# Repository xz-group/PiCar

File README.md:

PiCar Project
========================

Purpose
--------

The PiCar project is a miniature four-wheeled car powered by a Raspberry Pi 3 board. 
This lab-scale autonomous research platform is easy to build and modify. A camera and LIDAR mounted on the car allows for complex computer vision algorithms. 

This repository contains all the software and hardware source files required to duplicate the car, including:
* Chassis 3D printing, and CAD sources.
* Raspberry Pi 3 breakout PCB to connect peripherals and draw power from LiPo battery.
* Source code of the following sofware modules capable of:
 * Acquire wheel RPM data using encoder.
 * Acquire acceleration, angular velocity, and compass data from an I²C LSM9DS1 IMU.
 * Acquire video data from a Raspberry Pi NoIR camera.
 * Perform real-time computer vision using camera data.
 * Control the speed of brushed DC motor.

Documentation 
--------------
- http://picar.readthedocs.io (migration in progress)
- https://github.com/xz-group/PiCar/wiki (old)

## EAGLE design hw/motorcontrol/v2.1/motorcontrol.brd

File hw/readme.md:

The current version of the PiCar does not use a separate motor control board. 
Check documentation for hardware info.

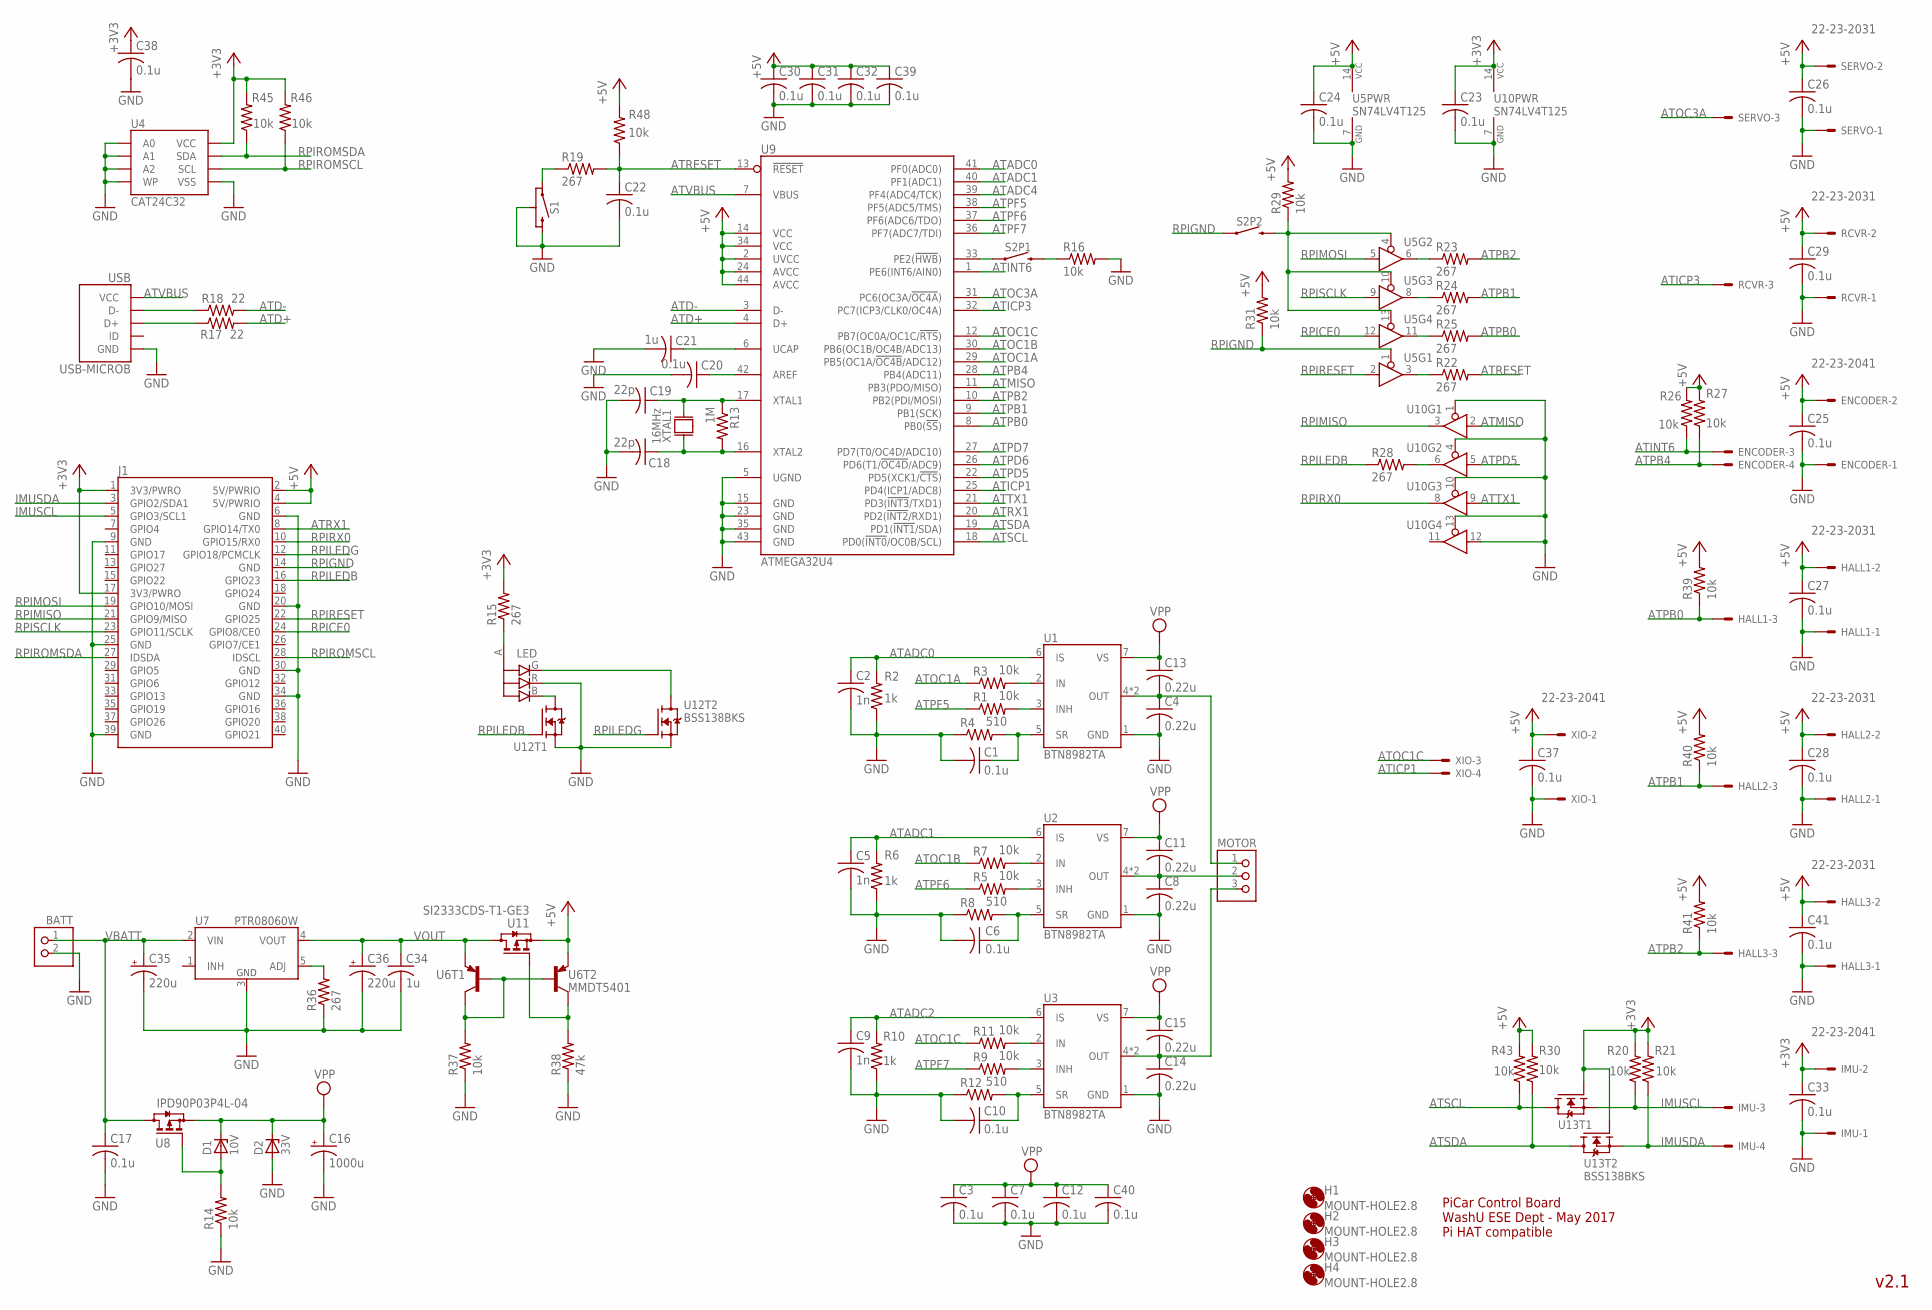
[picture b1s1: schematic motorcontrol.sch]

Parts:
BATT: ULTRAFIT_2CIRCVCLIP; ULTRAFIT_2CIRC_VERTCLIP
C1, C3, C6, C7, C10, C12, C17, C20, C22, C23, C24, C25, C26, C27, C28, C29, C30, C31, C32, C33, C37, C38, C39, C40, C41: 0.1u; C1206
C2, C5, C9: 1n; C1206
C4, C8, C11, C13, C14, C15: 0.22u; C1206
C16: 1000u; E5-10,5
C18, C19: 22p; C1206
C21, C34: 1u; C1206
C35, C36: 220u; E3,5-8
D1: 10V; SOD123
D2: 33V; SMA
ENCODER: 22-23-2041
H1, H2, H3, H4: MOUNT-HOLE2.8; 2,8
HALL1, HALL2, HALL3: 22-23-2031
IMU: 22-23-2041
J1: RPIHEADER_2.54-SMD; RPI_SMD
LED: LED_3COLOR_COMMONA1411; 150141M173100
MOTOR: ULTRAFIT_3CIRCVCLIP; ULTRAFIT_3CIRC_VERTCLIP
R1, R3, R5, R7, R9, R11, R14, R16, R20, R21, R26, R27, R29, R30, R31, R37, R39, R40, R41, R43, R45, R46, R48: 10k; R1206
R2, R6, R10: 1k; R1206
R4, R8, R12: 510; R1206
R13: 1M; R1206
R15, R19, R22, R23, R24, R25, R28, R36: 267; R1206
R17, R18: 22; R1206
R38: 47k; R1206
RCVR: 22-23-2031
S1: SWITCH-GND; B3F-312X
S2: A6HF-2DIP
SERVO: 22-23-2031
U1, U2, U3: BTN8982TA; TO263-7
U4: CAT24C32; SOIC8
U5, U10: SN74LV4T125; TSSOP14
U6: MMDT5401; SOT363
U7: PTR08060W; EDP_MODULE
U8: IPD90P03P4L-04; TO252-3-11
U9: ATMEGA32U4; TQFP44
U11: SI2333CDS-T1-GE3; SOT23-3
U12, U13: BSS138BKS; SOT363
USB: USB-MICROB; FCI-10103594-0001LF
XIO: 22-23-2041
XTAL1: 16MHz; ABLS7M2

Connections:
+3V3: C23.1, C33.1, C38.1, IMU.2, J1.1 (3V3/PWRO), J1.17 (3V3/PWRO), R15.2, R20.2, R21.2, R45.2, R46.2, U4.8 (VCC), U10.14 (VCC), U13.2 (G), U13.5 (G)
+5V: C24.1, C25.1, C26.1, C27.1, C28.1, C29.1, C30.1, C31.1, C32.1, C37.1, C39.1, C41.1, ENCODER.2, HALL1.2, HALL2.2, HALL3.2, J1.2 (5V/PWRIO), J1.4 (5V/PWRIO), R26.2, R27.2, R29.2, R30.2, R31.2, R39.2, R40.2, R41.2, R43.2, R48.2, RCVR.2, SERVO.2, U5.14 (VCC), U6.4 (E), U9.2 (UVCC), U9.14 (VCC), U9.24 (AVCC), U9.34 (VCC), U9.44 (AVCC), U11.2 (S), XIO.2
ATADC0: C2.1, R2.2, U1.6 (IS), U9.41 (PF0(ADC0))
ATADC1: C5.1, R6.2, U2.6 (IS), U9.40 (PF1(ADC1))
ATD+: R17.2, U9.4 (D+)
ATD-: R18.2, U9.3 (D-)
ATICP1: U9.25 (PD4(ICP1/ADC8)), XIO.4
ATICP3: RCVR.3, U9.32 (PC7(ICP3/CLK0/OC4A))
ATINT6: ENCODER.3, R26.1, U9.1 (PE6(INT6/AIN0))
ATMISO: U9.11 (PB3(PDO/MISO)), U10.2 (I)
ATOC1A: R3.1, U9.29 (PB5(OC1A/!OC4B!/ADC12))
ATOC1B: R7.1, U9.30 (PB6(OC1B/OC4B/ADC13))
ATOC1C: R11.1, U9.12 (PB7(OC0A/OC1C/!RTS!)), XIO.3
ATOC3A: SERVO.3, U9.31 (PC6(OC3A/!OC4A!))
ATPB0: HALL1.3, R25.2, R39.1, U9.8 (PB0(!SS!))
ATPB1: HALL2.3, R24.2, R40.1, U9.9 (PB1(SCK))
ATPB2: HALL3.3, R23.2, R41.1, U9.10 (PB2(PDI/MOSI))
ATPB4: ENCODER.4, R27.1, U9.28 (PB4(ADC11))
ATPD5: U9.22 (PD5(XCK1/!CTS!)), U10.5 (I)
ATPF5: R1.1, U9.38 (PF5(ADC5/TMS))
ATPF6: R5.1, U9.37 (PF6(ADC6/TDO))
ATPF7: R9.1, U9.36 (PF7(ADC7/TDI))
ATRESET: C22.1, R19.2, R22.2, R48.1, U9.13 (!RESET!)
ATRX1: J1.8 (GPIO14/TX0), U9.20 (PD2(!INT2!/RXD1))
ATSCL: R43.1, U9.18 (PD0(!INT0!/OC0B/SCL)), U13.6 (D)
ATSDA: R30.1, U9.19 (PD1(!INT1!/SDA)), U13.3 (D)
ATTX1: U9.21 (PD3(!INT3!/TXD1)), U10.9 (I)
ATVBUS: U9.7 (VBUS), USB.1 (VCC)
GND: BATT.2, C1.2, C2.2, C3.2, C4.2, C5.2, C6.2, C7.2, C8.2, C9.2, C10.2, C12.2, C14.2, C16.-, C17.2, C18.2, C19.2, C20.2, C21.2, C22.2, C23.2, C24.2, C25.2, C26.2, C27.2, C28.2, C29.2, C30.2, C31.2, C32.2, C33.2, C34.2, C35.-, C36.-, C37.2, C38.2, C39.2, C40.2, C41.2, D2.A, ENCODER.1, HALL1.1, HALL2.1, HALL3.1, IMU.1, J1.6 (GND), J1.9 (GND), J1.20 (GND), J1.25 (GND), J1.30 (GND), J1.34 (GND), J1.39 (GND), LED.R, R2.1, R4.1, R6.1, R8.1, R10.1, R12.1, R14.1, R16.2, R36.1, R37.1, R38.1, RCVR.1, S1.2, S1.3 (GND), S1.4 (GND), SERVO.1, U1.1 (GND), U2.1 (GND), U3.1 (GND), U4.1 (A0), U4.2 (A1), U4.3 (A2), U4.4 (VSS), U4.7 (WP), U5.7 (GND), U7.3 (GND), U9.5 (UGND), U9.15 (GND), U9.23 (GND), U9.35 (GND), U9.43 (GND), U10.1 (OE), U10.4 (OE), U10.7 (GND), U10.10 (OE), U10.12 (I), U10.13 (OE), U12.1 (S), U12.4 (S), USB.5 (GND), USB.GND1 (GND), USB.GND2 (GND), USB.GND3 (GND), USB.GND4 (GND), XIO.1
IMUSCL: IMU.3, J1.5 (GPIO3/SCL1), R20.1, U13.1 (S)
IMUSDA: IMU.4, J1.3 (GPIO2/SDA1), R21.1, U13.4 (S)
unnamed: R1.2, U1.3 (INH)
unnamed: R38.2, U6.3 (C), U11.1 (G)
unnamed: C19.1, R13.1, U9.17 (XTAL1), XTAL1.2
unnamed: R3.2, U1.2 (IN)
unnamed: C6.1, R8.2, U2.5 (SR)
unnamed: R5.2, U2.3 (INH)
unnamed: C18.1, R13.2, U9.16 (XTAL2), XTAL1.1
unnamed: S2.P1.1 (1), U9.33 (PE2(!HWB!))
unnamed: R7.2, U2.2 (IN)
unnamed: LED.A, R15.1
unnamed: R28.2, U10.6 (O)
unnamed: R16.1, S2.P1.2 (2)
unnamed: R37.2, U6.2 (B), U6.5 (B), U6.6 (C)
unnamed: LED.B, U12.6 (D)
unnamed: R9.2, U3.3 (INH)
unnamed: R18.1, USB.2 (D-)
unnamed: R11.2, U3.2 (IN)
unnamed: R22.1, U5.3 (O)
unnamed: C20.1, U9.42 (AREF)
unnamed: C21.1, U9.6 (UCAP)
unnamed: D1.A, R14.2, U8.1 (G)
unnamed: LED.G, U12.3 (D)
unnamed: R19.1, S1.1
unnamed: C1.1, R4.2, U1.5 (SR)
unnamed: R17.1, USB.3 (D+)
unnamed: C10.1, R12.2, U3.5 (SR)
unnamed: R23.1, U5.6 (O)
unnamed: R24.1, U5.8 (O)
unnamed: R25.1, U5.11 (O)
unnamed: R36.2, U7.5 (ADJ)
OUT1: C4.1, C13.2, MOTOR.1, U1.4 (OUT), U1.8 (OUT)
OUT2: C8.1, C11.2, MOTOR.2, U2.4 (OUT), U2.8 (OUT)
OUT3: C14.1, C15.2, MOTOR.3, U3.4 (OUT), U3.8 (OUT)
RPICE0: J1.24 (GPIO8/CE0), U5.12 (I)
RPIGND: J1.14 (GND), R31.1, S2.P2.1 (1), U5.1 (OE)
RPILEDB: J1.16 (GPIO23), R28.1, U12.2 (G)
RPILEDG: J1.12 (GPIO18/PCMCLK), U12.5 (G)
RPIMISO: J1.21 (GPIO9/MISO), U10.3 (O)
RPIMOSI: J1.19 (GPIO10/MOSI), U5.5 (I)
RPIRESET: J1.22 (GPIO25), U5.2 (I)
RPIROMSCL: J1.28 (IDSCL), R46.1, U4.6 (SCL)
RPIROMSDA: J1.27 (IDSDA), R45.1, U4.5 (SDA)
RPIRX0: J1.10 (GPIO15/RX0), U10.8 (O)
RPISCLK: J1.23 (GPIO11/SCLK), U5.9 (I)
U5OE: R29.1, S2.P2.2 (2), U5.4 (OE), U5.10 (OE), U5.13 (OE)
VBATT: BATT.1, C17.1, C35.+, U7.2 (VIN), U8.2 (D)
VOUT: C34.1, C36.+, U6.1 (E), U7.4 (VOUT), U11.3 (D)
VPP: C3.1, C7.1, C11.1, C12.1, C13.1, C15.1, C16.+, C40.1, D1.C, D2.C, U1.7 (VS), U2.7 (VS), U3.7 (VS), U8.3 (S)

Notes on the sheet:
PiCar Control Board WashU ESE Dept - May 2017 Pi HAT compatible
v2.1

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
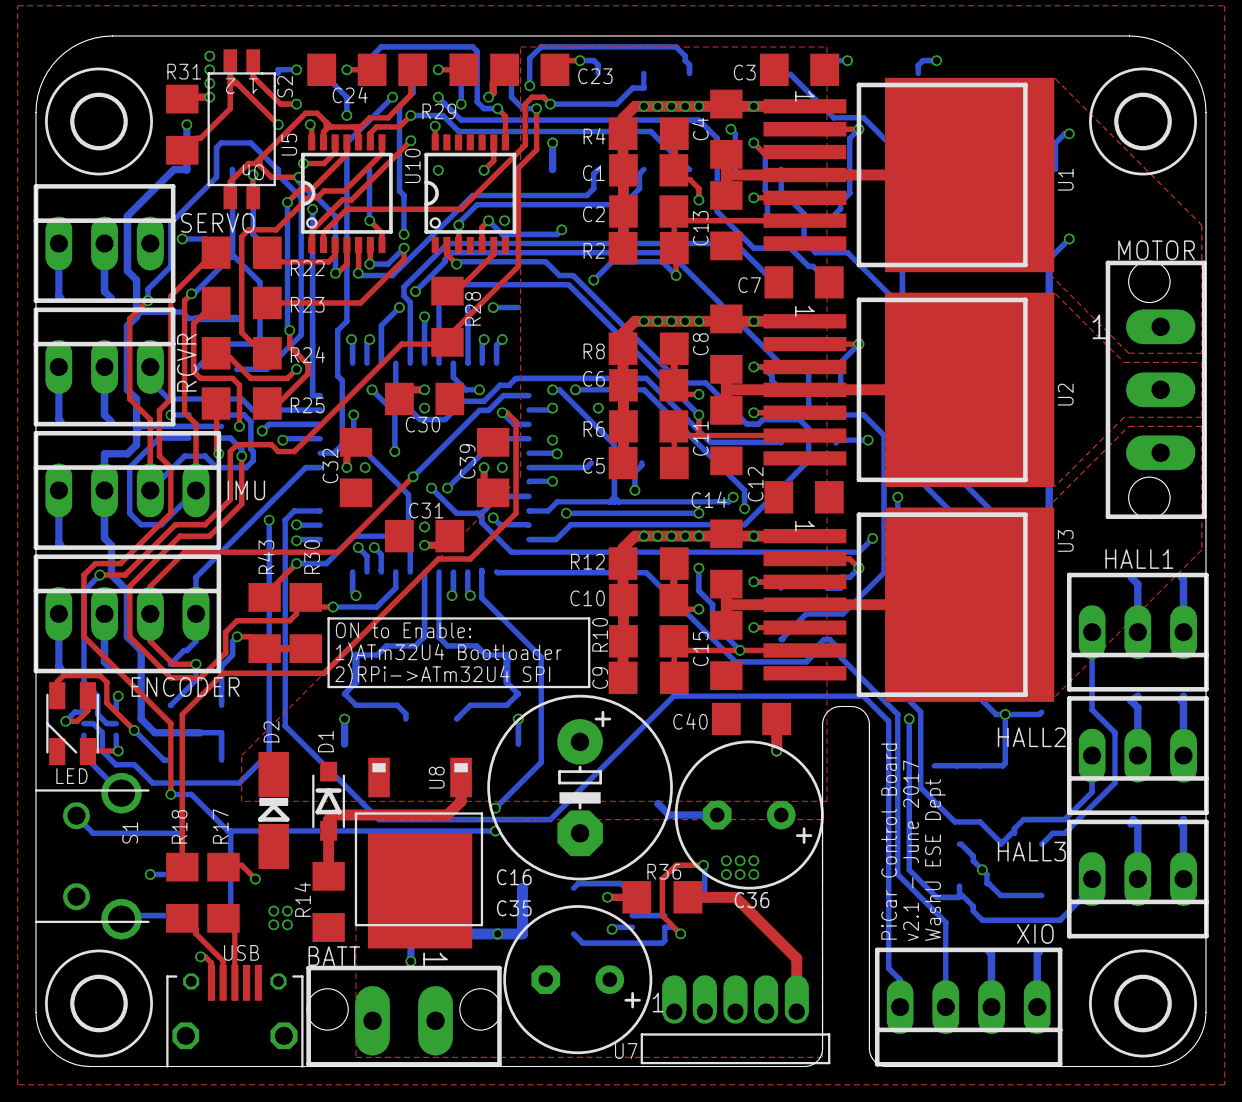
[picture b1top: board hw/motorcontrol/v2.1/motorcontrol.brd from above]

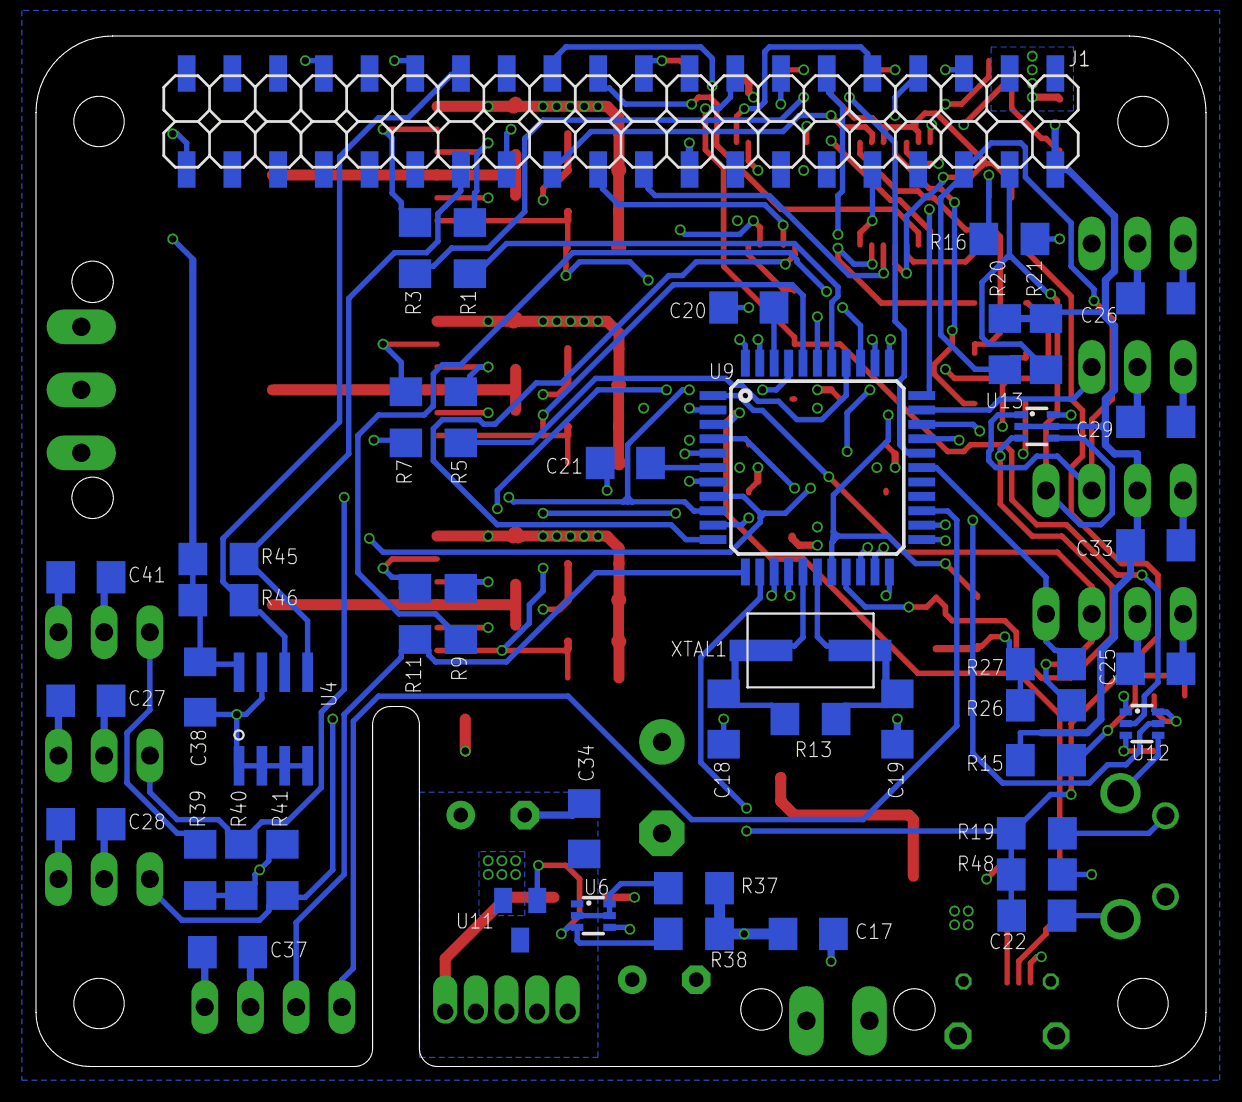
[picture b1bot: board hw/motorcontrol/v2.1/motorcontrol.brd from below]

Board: 4 copper layers, 65.0 x 57.2 mm, 117 parts (45 on the bottom side), 80 nets.

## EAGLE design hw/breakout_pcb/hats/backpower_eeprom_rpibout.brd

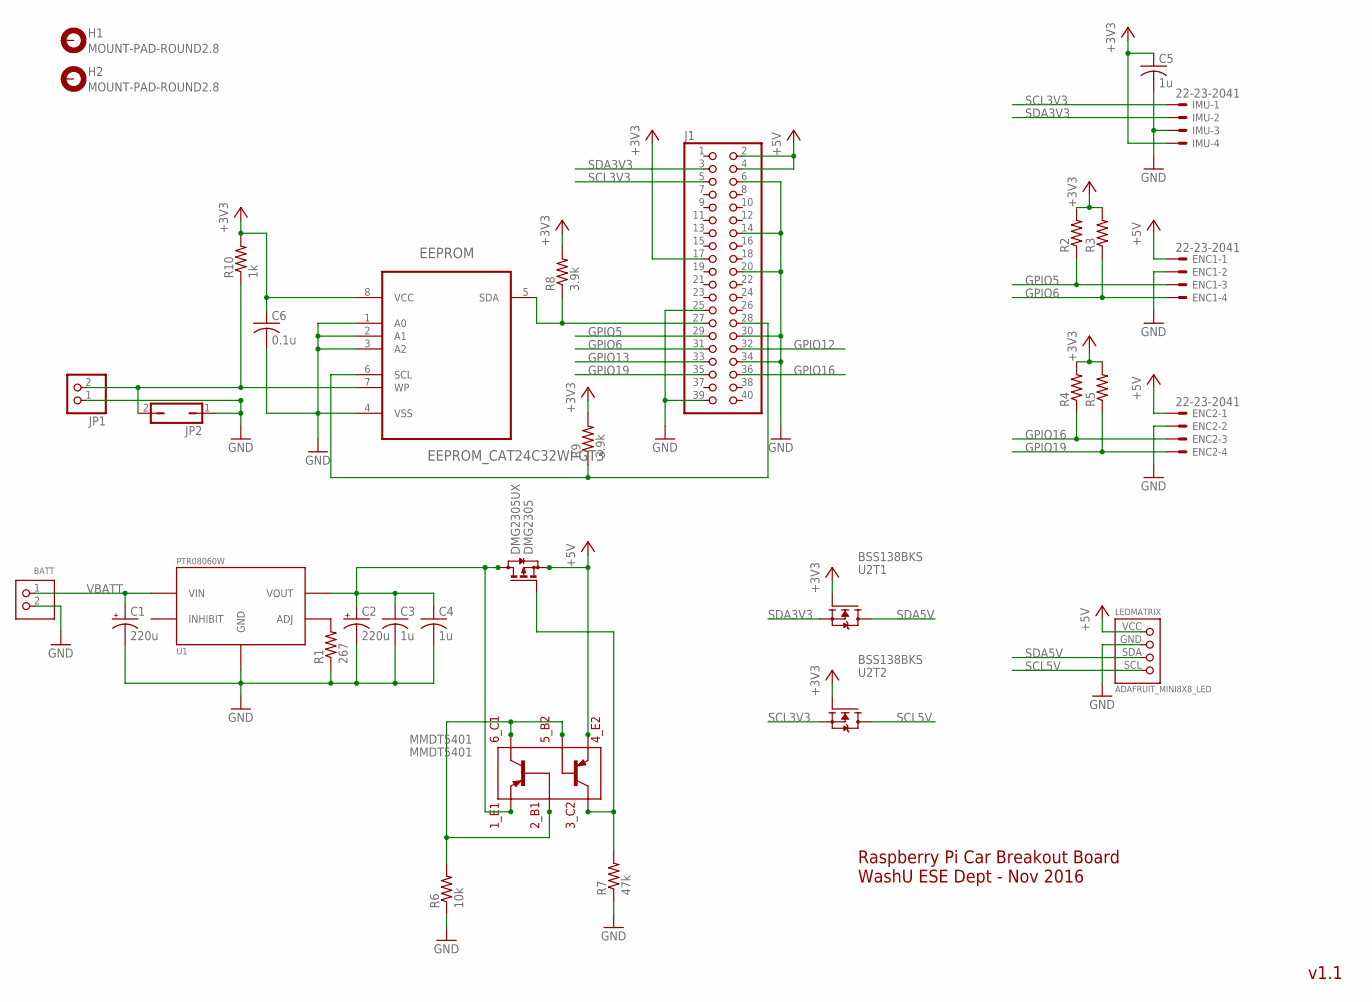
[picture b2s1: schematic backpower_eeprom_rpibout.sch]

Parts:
BATT: ULTRAFIT_2CIRC; ULTRAFIT_2CIRC_RANGLE
C1, C2: 220u; E3,5-8
C3, C4, C5: 1u; C1206
C6: 0.1u; C1206
DMG2305: DMG2305UX; SOT23-3
EEPROM: EEPROM_CAT24C32WI-GT3; SOIC-8
ENC1, ENC2: 22-23-2041
H1, H2: MOUNT-PAD-ROUND2.8; 2,8-PAD
IMU: 22-23-2041
J1: PINHD-2X20; 2X20
JP1: PINHD-1X2; 1X02
JP2: JP1Q; JP1
LEDMATRIX: ADAFRUIT_MINI8X8_LED; ADAFRUIT_MINI8X8_BACKPACK
MMDT5401: MMDT5401; SOT363
R1: 267; R1206
R2, R3, R4, R5: R-US_R1206; R1206
R6: 10k; R1206
R7: 47k; R1206
R8, R9: 3.9k; R1206
R10: 1k; R1206
U1: PTR08060W; EDP_MODULE
U2: BSS138BKS; SOT363

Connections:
+3V3: C5.1, C6.1, EEPROM.8 (VCC), IMU.4, J1.17, R2.2, R3.2, R4.2, R5.2, R8.2, R9.2, R10.2, U2.2 (G), U2.5 (G)
+5V: DMG2305.2 (S), ENC1.1, ENC2.1, J1.2, J1.4, LEDMATRIX.VCC, MMDT5401.1 (E1)
GND: BATT.2, C1.-, C2.-, C3.2, C4.2, C5.2, C6.2, EEPROM.1 (A0), EEPROM.2 (A1), EEPROM.3 (A2), EEPROM.4 (VSS), ENC1.2, ENC2.2, IMU.3, J1.6, J1.14, J1.20, J1.25, J1.30, J1.34, J1.39, JP1.1, JP2.1, LEDMATRIX.GND, R1.1, R6.1, R7.1, U1.P3 (GND)
GPIO5: ENC1.3, J1.29, R2.1
GPIO6: ENC1.4, J1.31, R3.1
GPIO12: J1.32
GPIO13: J1.33
GPIO16: ENC2.3, J1.36, R4.1
GPIO19: ENC2.4, J1.35, R5.1
unnamed: MMDT5401.2 (B1), MMDT5401.3 (C2), MMDT5401.5 (B2), R6.2
unnamed: R1.2, U1.P5 (ADJ)
unnamed: DMG2305.1 (G), MMDT5401.6 (C1), R7.2
unnamed: EEPROM.5 (SDA), J1.27, R8.1
unnamed: EEPROM.6 (SCL), J1.28, R9.1
unnamed: EEPROM.7 (WP), JP1.2, JP2.2, R10.1
SCL3V3: IMU.1, J1.5, U2.4 (S)
SCL5V: LEDMATRIX.SCL, U2.3 (D)
SDA3V3: IMU.2, J1.3, U2.1 (S)
SDA5V: LEDMATRIX.SDA, U2.6 (D)
VBATT: BATT.1, C1.+, U1.P2 (VIN)
VOUT: C2.+, C3.1, C4.1, DMG2305.3 (D), MMDT5401.4 (E2), U1.P4 (VOUT)

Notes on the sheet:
v1.1
Raspberry Pi Car Breakout Board WashU ESE Dept - Nov 2016

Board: 2 copper layers, 31 parts (0 on the bottom side), 19 nets, no tracks yet.

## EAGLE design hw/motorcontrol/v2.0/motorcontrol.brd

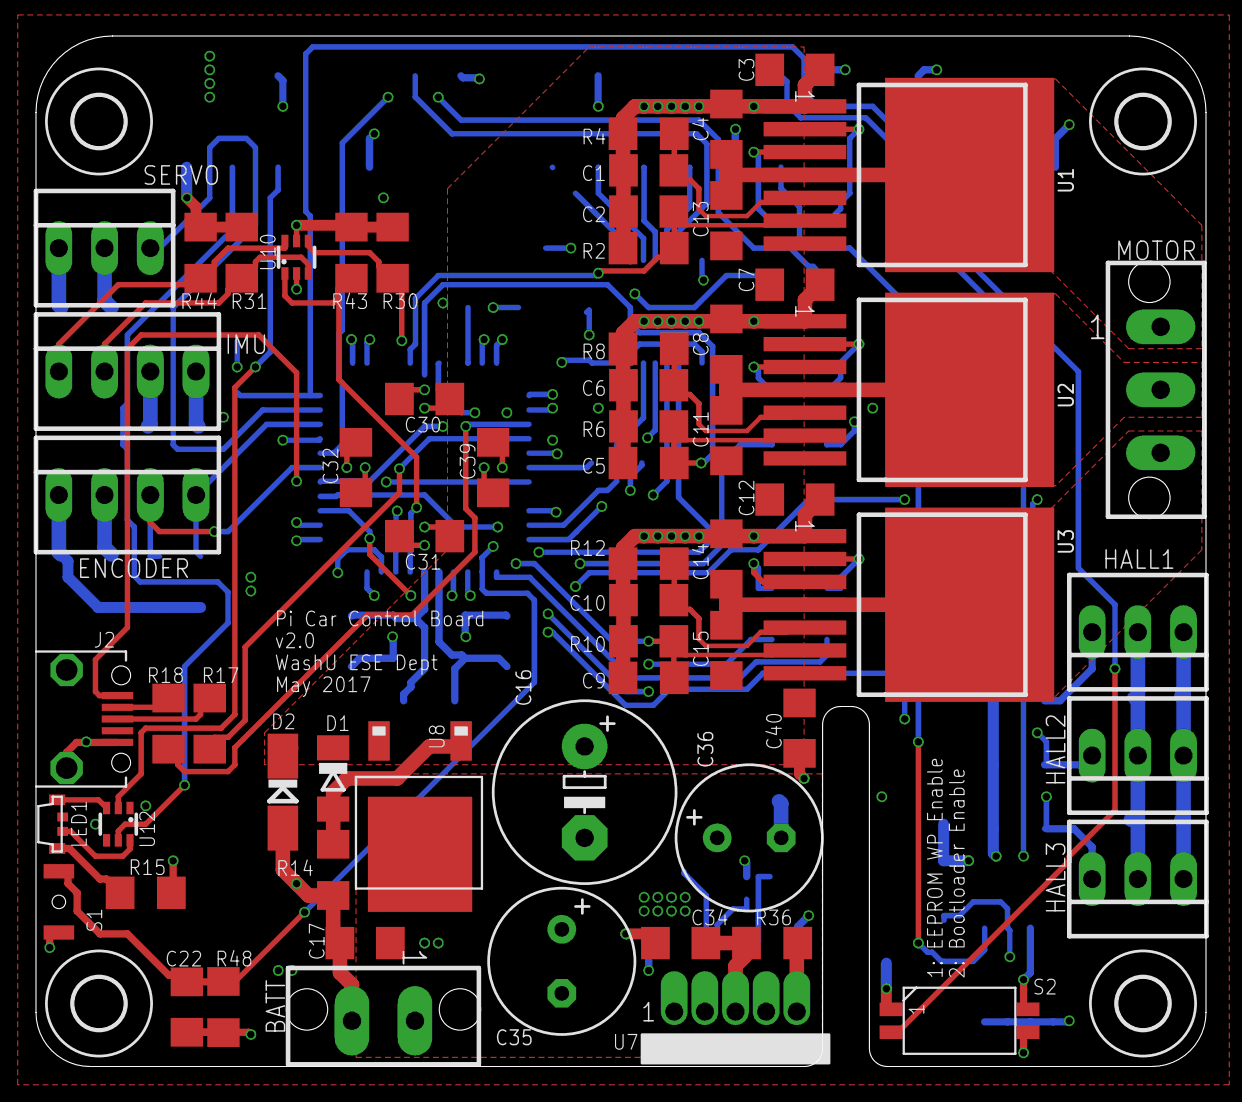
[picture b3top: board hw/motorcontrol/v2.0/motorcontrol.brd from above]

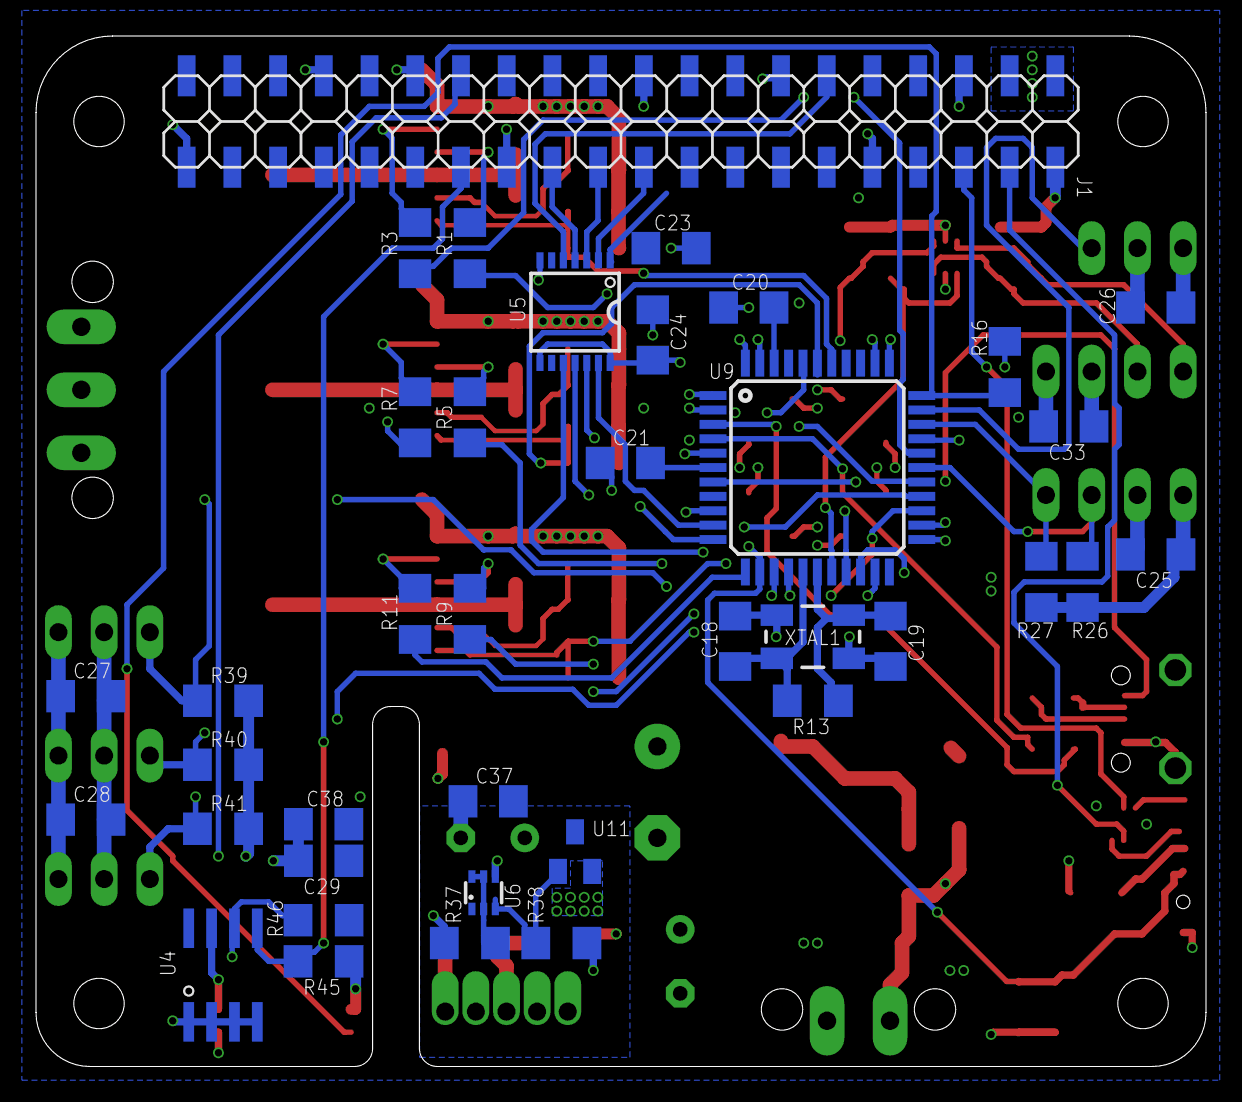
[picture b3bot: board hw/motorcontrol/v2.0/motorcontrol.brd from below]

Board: 4 copper layers, 65.0 x 57.2 mm, 105 parts (37 on the bottom side), 67 nets.

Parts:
BATT: ULTRAFIT_2CIRCVCLIP; ULTRAFIT_2CIRC_VERTCLIP
C1, C3, C6, C7, C10, C12, C17, C20, C22, C23, C24, C25, C26, C27, C28, C30, C31, C32, C33, C38, C39, C40: 0.1u; C1206
C2, C5, C9: 1n; C1206
C4, C8, C11, C13, C14, C15: 220n; C1206
C16: 1000u; E5-10,5
C18, C19: 22p; C1206
C21, C34, C37: 1u; C1206
C29: 10u; C1206
C35, C36: 220u; E3,5-8
D1: 10V; SOD80C
D2: 33V; SMA
ENCODER: 22-23-2041
H1, H2, H3, H4: MOUNT-HOLE2.8; 2,8
HALL1, HALL2, HALL3: 22-23-2031
IMU: 22-23-2041
J1: RPI_SMD
J2: USB-MICROB; FCI-10103594-0001LF
LED1: MSL0201RGB
MOTOR: ULTRAFIT_3CIRCVCLIP; ULTRAFIT_3CIRC_VERTCLIP
R1, R3, R5, R7, R9, R11, R14, R37, R39, R40, R41, R48: 10k; R1206
R2, R6, R10: 1k; R1206
R4, R8, R12, R15: 0.51k; R1206
R13: 1M; R1206
R16, R26, R27, R30, R31, R43, R44, R45, R46: 3.9k; R1206
R17, R18: 22; R1206
R36: 267; R1206
R38: 47k; R1206
S1: B3U-3000P-B
S2: A6HF-2DIP; A6HF
SERVO: 22-23-2031
U1, U2, U3: BTN8982TA; TO263-7
U4: CAT24C32WI-GT3; SOIC8
U5: ADG3304; TSSOP14
U6: MMDT5401; SOT363
U7: PTR08060W; EDP_MODULE
U8: IPD90P03P4L-04; TO252-3-11
U9: ATMEGA32U4; TQFP44
U10, U12: BSS138BKS; SOT363
U11: DMG2305UX; SOT23-3
XTAL1: 16MHz; ABM3B

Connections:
+3V3: C23.1, C29.1, C33.1, C38.1, IMU.3, J1.1, J1.17, R15.2, R31.2, R44.2, R45.2, R46.2, S2.P1.1, U4.8, U5.1
+5V: C22.1, C24.1, C25.1, C26.1, C27.1, C28.1, C30.1, C31.1, C32.1, C39.1, ENCODER.1, HALL1.1, HALL2.1, HALL3.1, J1.2, J1.4, R16.2, R26.2, R27.2, R30.2, R39.2, R40.2, R41.2, R43.2, R48.2, SERVO.2, U5.8, U5.14, U6.4, U9.2, U9.14, U9.24, U9.34, U9.44, U10.2, U10.5, U11.2
A2: C2.1, R2.2, U1.6, U9.38
A3: C5.1, R6.2, U2.6, U9.39
A4: C9.1, R10.2, U3.6, U9.40
ATMEGAMISO: U5.12, U9.11
ATMEGAMOSI: U5.13, U9.10
ATMEGARESET: C22.2, R48.1, S1.2, U5.10, U9.13
ATMEGASCK: U5.11, U9.9
ATMEGASCL: R43.1, U9.18, U10.1
ATMEGASDA: R30.1, U9.19, U10.4
D0: HALL1.3, R39.1, U9.20
D1: HALL2.3, R40.1, U9.21
D4: R9.1, U9.25
D5: ENCODER.4, R27.1, U9.31
D6: R1.1, U9.27
D7: HALL3.3, R41.1, U9.1
D8: ENCODER.3, R26.1, U9.28
D9: R3.1, U9.29
D10: R7.1, U9.30
D11: R11.1, U9.12
D12: R5.1, U9.26
D13: SERVO.3, U9.32
GND: BATT.2, C1.2, C2.2, C3.2, C4.2, C5.2, C6.2, C7.2, C8.2, C9.2, C10.2, C12.2, C14.2, C16.-, C17.2, C18.2, C19.2, C20.2, C21.2, C23.2, C24.2, C25.2, C26.2, C27.2, C28.2, C29.2, C30.2, C31.2, C32.2, C33.2, C34.2, C35.-, C36.-, C37.2, C38.2, C39.2, C40.2, D2.A, ENCODER.2, HALL1.2, HALL2.2, HALL3.2, IMU.4, J1.6, J1.9, J1.14, J1.20, J1.25, J1.30, J1.34, J1.39, J2.5, J2.GND1, J2.GND2, LED1.R, R2.1, R4.1, R6.1, R8.1, R10.1, R12.1, R14.1, R36.1, R37.1, R38.1, S1.1, S2.P2.2, SERVO.1, U1.1, U2.1, U3.1, U4.1, U4.2, U4.3, U4.4, U5.7, U7.P3, U9.5, U9.15, U9.23, U9.35, U9.43, U12.1, U12.4, XTAL1.GND2, XTAL1.GND4
IMUSCL: IMU.1, R44.1, U10.6
IMUSDA: IMU.2, R31.1, U10.3
unnamed: R1.2, U1.3
unnamed: R38.2, U6.3, U11.1
unnamed: C18.1, R13.1, U9.16, XTAL1.P3
unnamed: R3.2, U1.2
unnamed: C1.1, R4.2, U1.5
unnamed: R5.2, U2.3
unnamed: C19.1, R13.2, U9.17, XTAL1.P1
unnamed: R16.1, S2.P2.1, U9.33
unnamed: R7.2, U2.2
unnamed: LED1.A, R15.1
unnamed: C6.1, R8.2, U2.5
unnamed: S2.P1.2, U4.7
unnamed: R37.2, U6.2, U6.5, U6.6
unnamed: LED1.B, U12.6
unnamed: R9.2, U3.3
unnamed: J2.2, R18.1
unnamed: R11.2, U3.2
unnamed: C10.1, R12.2, U3.5
unnamed: C20.1, U9.42
unnamed: C21.1, U9.6
unnamed: D1.A, R14.2, U8.1
unnamed: LED1.G, U12.3
unnamed: R18.2, U9.3
unnamed: R17.2, U9.4
unnamed: J2.3, R17.1
unnamed: R36.2, U7.P5
OUT1: C4.1, C13.2, MOTOR.1, U1.4, U1.8
OUT2: C8.1, C11.2, MOTOR.2, U2.4, U2.8
OUT3: C14.1, C15.2, MOTOR.3, U3.4, U3.8
RPILEDB: J1.5, U12.2
RPILEDG: J1.3, U12.5
RPIMISO: J1.21, U5.3
RPIMOSI: J1.19, U5.2
RPIRESET: J1.12, U5.5
RPIROMSCL: J1.28, R46.1, U4.6
RPIROMSDA: J1.27, R45.1, U4.5
RPISCK: J1.23, U5.4
VBATT: BATT.1, C17.1, C35.+, U7.P2, U8.2
VBUS: J2.1, U9.7
VOUT: C34.1, C36.+, C37.1, U6.1, U7.P4, U11.3
VPP: C3.1, C7.1, C11.1, C12.1, C13.1, C15.1, C16.+, C40.1, D1.C, D2.C, U1.7, U2.7, U3.7, U8.3

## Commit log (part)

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2017-05-13 backup
2017-05-13 board is completely routed and checked
2017-05-13 names moved to final positions
2017-05-13 labels and text in place
2017-05-13 fixed font in top board layer
2017-05-13 fixed camera cable slot dimensions, there was nothing right about them (didn't follow pihat standard, didn't work for oshpark)
2017-05-14 updated schematic with new INH control
2017-05-14 rerouted INH signals
2017-05-14 added Sunstone Gerbers
2017-05-14 minor font change
2017-05-15 added Sunstone CAM files, eagle's BOM
2017-05-15 cut out is gone, long live the snake border
2017-05-15 updated gerbers
2017-05-15 motor control
2017-05-15 Create ArduinoAPI
2017-05-15 moved arduino API doc to docs folder
2017-05-15 moved motorcontrol arduino code to correct folder
2017-05-15 moved SPI code to arduino folder
2017-05-15 moved optical flow code to pi folder
2017-05-15 optical flow code
2017-05-15 removed old folder
2017-05-15 ttc calculations
2017-05-15 reduced noise histogram equalization
2017-05-16 template for data share headers
2017-05-16 basic dshare functionality
2017-05-16 TTC Calculated - see plot in folder
2017-05-16 Add files via upload
    Paper used to calculate ttc
2017-05-16 removed useless files
2017-05-16 Started header files
2017-05-17 motorcontrol
2017-05-17 primitive control started
2017-05-17 Servo Dshare added
2017-05-17 Servo Dshare Pi side added
2017-05-17 Deleted unnecessary files
2017-05-17 Working on linking
2017-05-17 moved sketch file
2017-05-17 Moved dshare.c file
2017-05-17 Moved header files
2017-05-17 Moved header files back
2017-05-17 built servo executable
2017-05-17 updated dshare
2017-05-18 minor changes to main file
2017-05-18 moved files to make Arduino IDE happy. Added avrfix.pdf thesis
2017-05-18 added avrfix
2017-05-18 fixed header function declarations
2017-05-18 added PID library
2017-05-18 small changes
2017-05-18 motor
2017-05-18 motorcontrol with interrupts
2017-05-18 fixed merge corruption, autoformatted all source files
2017-05-18 created fixed point wrapper header, updated PID code
2017-05-18 added fp to other datatypes macros
2017-05-18 motorcontrol read hall sensors
2017-05-18 improved PID code, added second order Butterworth IIR filter
2017-05-19 bldc interrupt
2017-05-19 bldc
2017-05-19 pinout
2017-05-19 pcb bldc
2017-05-20 added pdfs to help with assembly
2017-05-20 minor cosmetic changes to board
2017-05-20 Added RPMtoPWM function
    Haven't implemented PID yet.
2017-05-20 added IMU library
2017-05-20 added imu code
2017-05-20 added SPI interrupts
2017-05-20 moved imu library files
2017-05-20 Renamed to speed_control
    Input - RPM_desired
    Output - PWM
    Haven't implemented PID
2017-05-20 Fixed implicit function declarations
2017-05-20 spi communication edits
2017-05-21 fixing imu c issue
2017-05-21 imu.cpp code moved to Sparkfun's imu driver
2017-05-21 renamed Sparkfun's driver to simply imu
2017-05-21 imu does not compute float version of biases
2017-05-21 changed included header to imu.h
2017-05-21 removed shady imu calibration constant
2017-05-21 Modified FOE
2017-05-21 added PID windup protection, other minor changes
2017-05-21 changed imu code to read ints into main data structure
2017-05-21 Simple 'P'ID test
2017-05-21 Rename README.md.txt to README.md
2017-05-21 Clustering
2017-05-22 reenabled interrupts in PCB_BLDC code
2017-05-22 reorganization eagle files
2017-05-22 added arduino optical flow demo code
2017-05-22 small update to servo spi test
2017-05-22 list of changes for board items
2017-05-22 creating python spi protocol
2017-05-22 python spi test from arduino side
2017-05-22 python spi from pi side
2017-05-23 P control implemented
    Needs some more tuning. Need to implement 'I'
2017-05-23 added avrdude script
2017-05-24 primitive closed loop added
2017-05-24 new schematic is ready
2017-05-24 fixed RPi-Arduino buffer for reset pin
2017-05-24 added eepromutils for Pi HAT
2017-05-24 added gitignore to avoid commiting compiled files
2017-05-24 added eeprom HAT blob
2017-05-25 modified arduino spi test
2017-05-25 updated optical flow close loop test
2017-05-25 added new SPI procedure to main arduino file
2017-05-25 updated license
2017-05-25 added si23333cd_p datasheet
2017-05-25 updated layer display in v2.0 board
2017-05-25 modified pi control algorithim
2017-05-26 modified demo file
2017-05-26 attempted backing up code
2017-05-26 bldc test
2017-05-26 pcb test
2017-05-26 before autoroute
2017-05-26 temperary_current test
2017-05-27 implemented demo with dshare
2017-05-27 modified demo
2017-05-27 added PID controller for servo angle
2017-05-27 new bldc test
2017-05-27 fixed PWM to zero bug
2017-05-27 Updated PCB
2017-05-27 testing ability to add constant turning angle to demo
2017-05-28 added ability to change angle set point to demo
2017-05-28 Update to test on Pi via AVRdude
2017-05-28 implemented PI pwm controller, start condition
2017-05-28 attempting clustering
2017-05-28 deleted constFOE.avi
2017-05-28 Matt's changes
2017-05-28 updated PCB_test
2017-05-28 added bldc_enable bit
2017-05-28 added clustering
2017-05-28 created gitignore to avoid looking at video files
2017-05-28 added kill switch test
2017-05-28 Conflict corrected
2017-05-28 PCB SPI testing added
2017-05-29 Clustering is Diggggity Doneee
2017-05-29 improved demo
2017-05-29 Updated Demo
2017-05-29 minor arduino changes
2017-05-29 copied arduino file to make arduino leonardo file
2017-05-29 deleted leonardo file
2017-05-29 new sd card check
2017-05-29 Following demo code
2017-05-29 added avrdude config file
2017-05-29 Cluster density accounted for
2017-05-29 modified follow demo
2017-05-31 fixed typo in filename
2017-06-01 cleaned up code
2017-06-01 routed board
2017-06-01 board is ready
2017-06-02 final minor changes, added PDFs with board and schematic
2017-06-02 added BOM, minor package upgrades
2017-06-02 moved motorcontrol v2.1 to its own folder
2017-06-02 arduino_pcb
2017-06-03 fixed error in connection between IS U3 and ATADC4
2017-06-03 reorganized names in board
2017-06-03 updated diagrams
2017-06-30 Update lk_ttc_constantFOEcloselooptest.py
    Cleaned up Code
2017-07-01 Created gerber files
    Used gerb274x-4layer.cam file as recommened by Advanced Circuits (4pcb)
2017-07-02 added changelog and v2.0 errata
2017-07-02 minor improvement
2017-07-03 increased global PCB clearance to 6 mil
2017-12-21 PCB code update
2017-12-21 PCB code test
2018-02-26 stereo, tracking
2018-02-26 bouncing video
2018-02-26 tracking and stereo
2018-02-26 YOLO
2018-02-27 Updated readme
    Added wiki link and removed MoCap info.
2018-03-01 yolo --> tracker
2018-03-05 organized
2018-03-06 retrack failures
2018-03-06 retrack
2018-03-06 print status
2018-03-06 print
2018-03-06 finding specific objects
2018-03-06 separated files
2018-04-04 alias commit
2018-04-04 medianflow adaptive tracking
2018-04-10 Script to record videos
2018-04-11 feature matching and keypoint finder abstraction
2018-04-16 report generator, data acquisition, error calculations, lots of minor edits
2018-04-16 report generator finished
2018-04-27 comm_scripts
    Files from Patrick Naughton's communication module.
2018-04-30 cleaned up optical flow code
2018-04-30 restructured CV code, removed unused tracking files
2018-04-30 moved click file
2018-04-30 renamed folder
2018-04-30 readme 1
2018-04-30 README 2
2018-05-20 moved Sam & Moira's research reports into docs/reports
2018-05-21 started comprehensive documentation
2018-05-21 updated linux and github docs
2018-05-21 updated main readme
2018-05-21 added more tutorials for readthedocs
2018-05-21 added changelogs
2018-05-21 added note in ../readthedocs/../readthedocs_tut
2018-05-21 minor fixes to the docs
2018-05-21 Jerry K commit test contributor added
2018-05-21 minor docs fixes
2018-05-21 updated readme to reflect new docs
2018-05-21 Revert "Sync"
2018-05-21 Revert "Revert 1 master"
2018-05-22 updated Linux tutorial, Mechanical docs, and fixed formatting
2018-05-22 I2C communication docs
2018-05-23 PI to IMU implemented and documented
2018-05-24 updated docs
2018-05-24 Pi and Lidar Communication
2018-05-25 formatting
2018-05-25 fixed links in docs, formatting, etc.
2018-05-25 new i2c-dev file
2018-05-27 Added tutorial page for Python
2018-05-28 docs badge
2018-05-29 datasheet
2018-05-29 good datasheet
2018-06-01 added github button, added motor_feedback_control arduino code in src/arduino
2018-06-01 datasheet/socket code usage under software
2018-06-02 add IMU communication by LSM9DS1 Libray
2018-06-04 add sensors reading,writing and camera usage
2018-06-07 updated 'results' with imu_nav and power_mgmt reports
2018-06-07 changed relative links to permanent links
2018-06-07 version1 timer
2018-06-07 add sensor/camera concurrent reading by timer
2018-06-07 Updated Contributors
2018-06-07 added Syncing a Fork instructions for Github
2018-06-08 added Optical Flow to results
2018-06-12 update SPI tutorial between pi and arduino
2018-06-12 setFunctionEnabled
2018-06-15 IMU setting enabled Delta timing Lidar IMU implemented socket video stream implemented
2018-06-17 i2c by GPIO, sending float by i2c
2018-06-19 tempu
2018-06-19 delta time good, document added
2018-06-20 organized code and documentation in Electronics
2018-06-20 True data logging alpha
2018-06-20 My bad, truly the true alpha logging
2018-06-20 Serial communication between pi and arduino, organized documentation
2018-06-22 spi communication updated, tfmini lidar usage updated
2018-06-22 socketfoldertranfer
2018-06-22 socket folder transfer documented
2018-06-25 revision
2018-06-27 change
2018-06-27 folder reorganization
2018-06-27 betafinish
2018-06-27 server comment
2018-06-27 Internet section added server code in IMU folder
2018-06-27 Sorry, small correction
2018-06-29 add github links for Daniel and Karina
2018-07-02 add class to data logging
2018-07-02 silly mistake
2018-07-02 you win
2018-07-02 to pi
2018-07-03 goodsensors
2018-07-03 sensors change to devices finished with help message
2018-07-05 statetrial
2018-07-06 Adding the WASD arduino and pi code to github
2018-07-09 Updated WASD Code with incremental steering and command control times
2018-07-10 change to unix time instead of human readable format
2018-07-10 pmureadingadded
2018-07-12 data sychronization and display documentation
2018-07-13 folder organized pmu refined
2018-07-16 test
2018-07-16 remote transfer
2018-07-16 pmu tested
2018-07-17 documents for data logging combining logging with computer vision code
2018-07-18 update data plot and i2c bus0 usage
2018-07-19 Made a seperate folder for all movement control code
2018-07-19 fixed merge conlict
2018-07-19 fixed broken link for mobile movement control
2018-07-19 hope its alright
2018-07-19 fixed readthedocs conf file
2018-07-19 devices_int to picar change module dependency
2018-07-23 make html here
2018-07-23 organize code and update comment
2018-07-23 Added youtube links to picar videos
2018-07-25 add a missing file
2018-07-25 enable time search in data visualization
2018-07-30 fixed computer_vision code and moved from obsolete to src/pi
2018-09-04 updated mechanical assembly docs
2018-09-17 Added Getting Started Page
2018-10-10 Fixed documentation and organized old code
2018-12-11 Adding PiCar SLAM
2019-01-02 fixed docs
